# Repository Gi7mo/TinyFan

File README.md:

# Klipper TinyFan

### Navigation:
|[• Installation & Klipper](./Klipper)|[• Get a PCB](./PCB)|[• Mounts](./STL)|
|---|---|---|

|[• CAD Files](./CAD)|[• Manual](./TinyFan_Pinout.pdf)|[• Pictures](./Images)|
|---|---|---|
<br>

**ATTENTION**<br>
The LDO is flipped in the image, please don't mount it with the fin outward the pcb<br>
it must be mounted inward, so 180° flipped to shown in the image

<br>

## Notes
- Many thanks to [Rama](https://github.com/Ramalama2) who came up with the initial idea and supported me a lot.
- You can contact me via Discord "Gi7mo!#4618"
- This project does not come with any warranty, if you choose to build/use one, you are doing this at your own risk!

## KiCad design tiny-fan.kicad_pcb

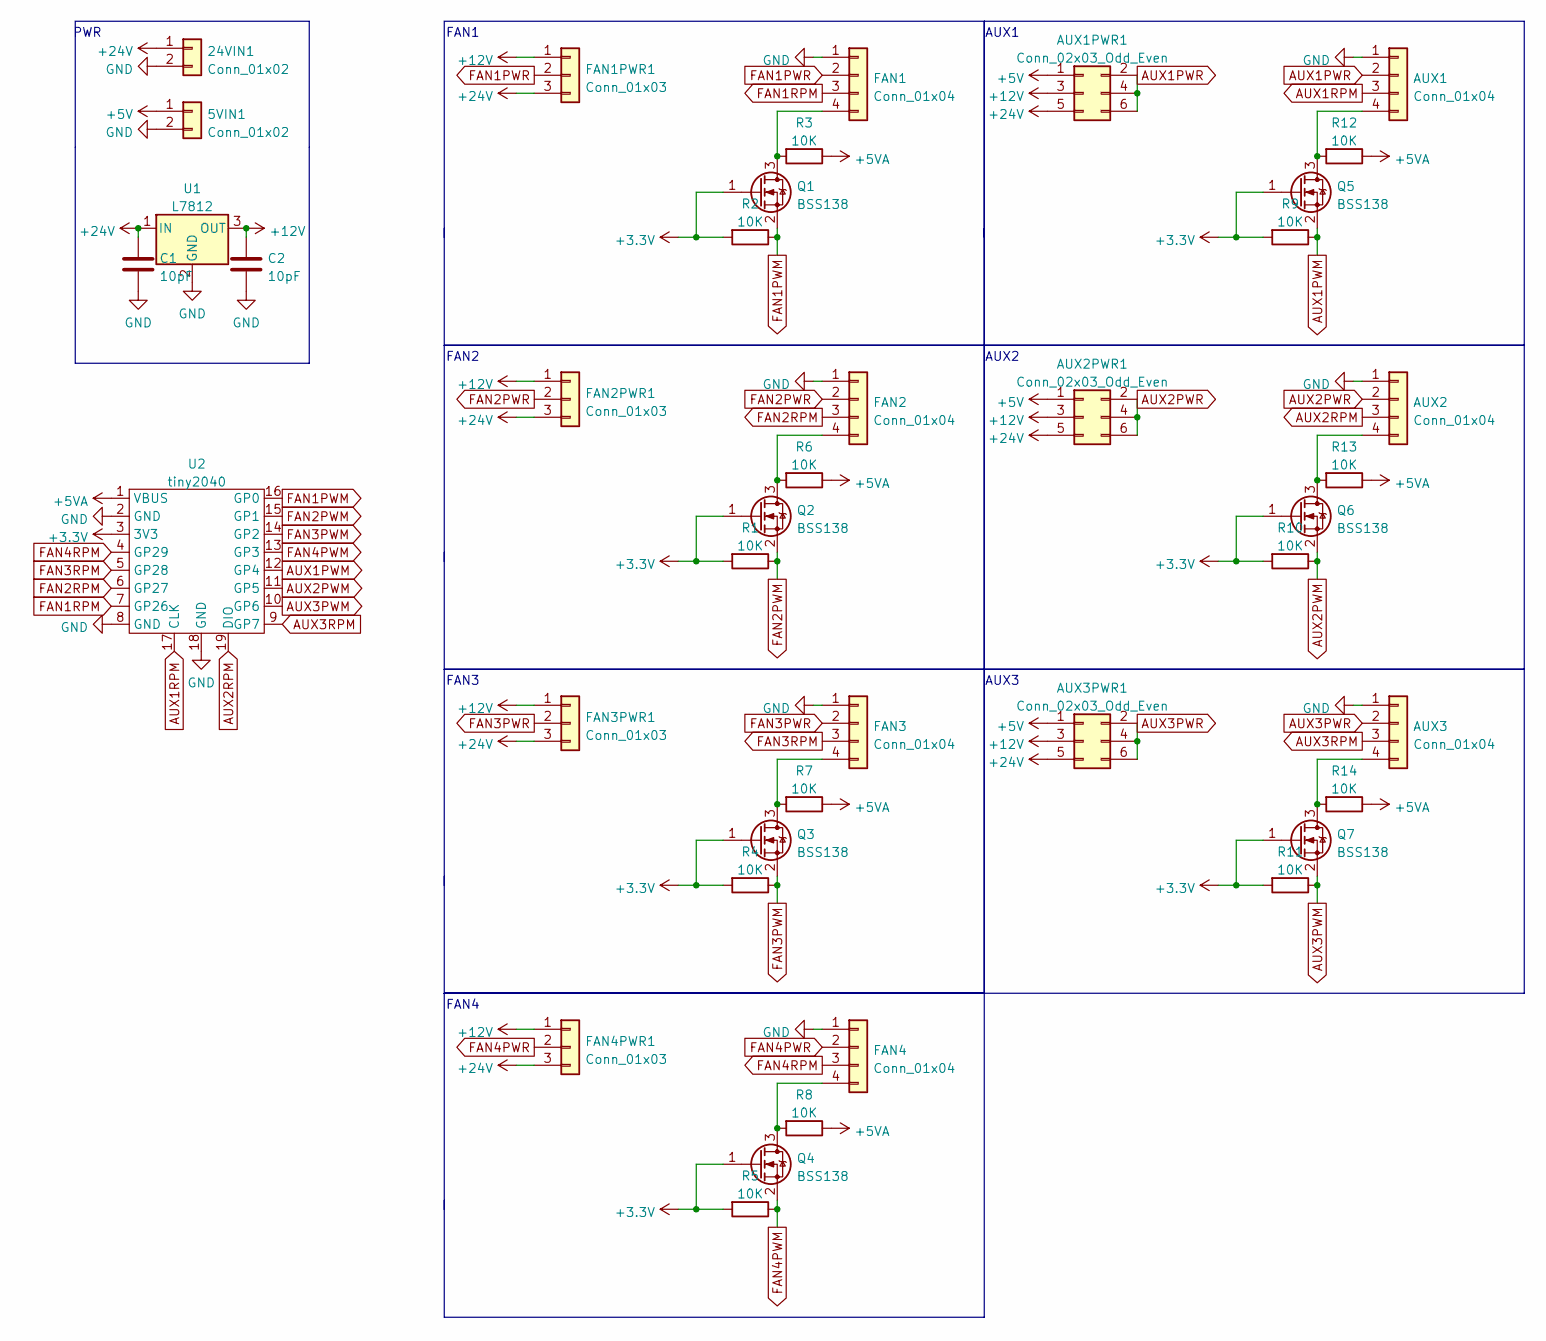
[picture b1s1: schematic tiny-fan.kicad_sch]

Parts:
5VIN1, 24VIN1: Conn_01x02; TerminalBlock_Phoenix_MKDS-1,5-2-5.08_1x02_P5.08mm_Horizont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; LCSC C475092
AUX1, AUX2, AUX3: Conn_01x04; JST_XH_B4B-XH-AM_1x04_P2.50mm_Vertical; LCSC C161871
AUX1PWR1, AUX2PWR1, AUX3PWR1: Conn_02x03_Odd_Even; PinHeader_2x03_P2.54mm_Vertical; LCSC C492420
C1, C2: 10pF; C_1206_3216Metric; LCSC C107172
FAN1, FAN2, FAN3, FAN4: Conn_01x04; FanPinHeader_1x04_P2.54mm_Vertical; LCSC C402778
FAN1PWR1, FAN2PWR1, FAN3PWR1, FAN4PWR1: Conn_01x03; PinHeader_1x03_P2.54mm_Vertical; LCSC C2937625
Q1, Q2, Q3, Q4, Q5, Q6, Q7: BSS138; SOT-23; LCSC C52895
R1, R2, R3, R4, R5, R6, R7, R8, R9, R10, R11, R12, R13, R14: 10K; R_1206_3216Metric; LCSC C144471
U1: L7812; TO-220-3; LCSC C105651
U2: tiny2040

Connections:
+3V3: Q1.1 (G), Q2.1 (G), Q3.1 (G), Q4.1 (G), Q5.1 (G), Q6.1 (G), Q7.1 (G), R1.2, R2.2, R4.2, R5.2, R9.2, R10.2, R11.2, U2.3 (3V3)
+5V: 5VIN1.1, AUX1PWR1.1, AUX2PWR1.1, AUX3PWR1.1
+5VA: R3.1, R6.1, R7.1, R8.1, R12.1, R13.1, R14.1, U2.1 (VBUS)
+12V: AUX1PWR1.3, AUX2PWR1.3, AUX3PWR1.3, C2.1, FAN1PWR1.1, FAN2PWR1.1, FAN3PWR1.1, FAN4PWR1.1, U1.3 (OUT)
+24V: 24VIN1.1, AUX1PWR1.5, AUX2PWR1.5, AUX3PWR1.5, C1.1, FAN1PWR1.3, FAN2PWR1.3, FAN3PWR1.3, FAN4PWR1.3, U1.1 (IN)
AUX1PWM: Q5.2 (S), R9.1, U2.12 (GP4)
AUX1PWR: AUX1.2, AUX1PWR1.2, AUX1PWR1.4, AUX1PWR1.6
AUX1RPM: AUX1.3, U2.17 (CLK)
AUX2PWM: Q6.2 (S), R10.1, U2.11 (GP5)
AUX2PWR: AUX2.2, AUX2PWR1.2, AUX2PWR1.4, AUX2PWR1.6
AUX2RPM: AUX2.3, U2.19 (DIO)
AUX3PWM: Q7.2 (S), R11.1, U2.10 (GP6)
AUX3PWR: AUX3.2, AUX3PWR1.2, AUX3PWR1.4, AUX3PWR1.6
AUX3RPM: AUX3.3, U2.9 (GP7)
FAN1PWM: Q1.2 (S), R2.1, U2.16 (GP0)
FAN1PWR: FAN1.2, FAN1PWR1.2
FAN1RPM: FAN1.3, U2.7 (GP26)
FAN2PWM: Q2.2 (S), R1.1, U2.15 (GP1)
FAN2PWR: FAN2.2, FAN2PWR1.2
FAN2RPM: FAN2.3, U2.6 (GP27)
FAN3PWM: Q3.2 (S), R4.1, U2.14 (GP2)
FAN3PWR: FAN3.2, FAN3PWR1.2
FAN3RPM: FAN3.3, U2.5 (GP28)
FAN4PWM: Q4.2 (S), R5.1, U2.13 (GP3)
FAN4PWR: FAN4.2, FAN4PWR1.2
FAN4RPM: FAN4.3, U2.4 (GP29)
GND: 5VIN1.2, 24VIN1.2, AUX1.1, AUX2.1, AUX3.1, C1.2, C2.2, FAN1.1, FAN2.1, FAN3.1, FAN4.1, U1.2 (GND), U2.2 (GND), U2.8 (GND), U2.18 (GND); also elsewhere on the board
unnamed: AUX1.4, Q5.3 (D), R12.2
unnamed: AUX2.4, Q6.3 (D), R13.2
unnamed: AUX3.4, Q7.3 (D), R14.2
unnamed: FAN1.4, Q1.3 (D), R3.2
unnamed: FAN2.4, Q2.3 (D), R6.2
unnamed: FAN3.4, Q3.3 (D), R7.2
unnamed: FAN4.4, Q4.3 (D), R8.2

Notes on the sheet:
AUX3
FAN1
AUX1
AUX2
FAN4
FAN3
FAN2
PWR

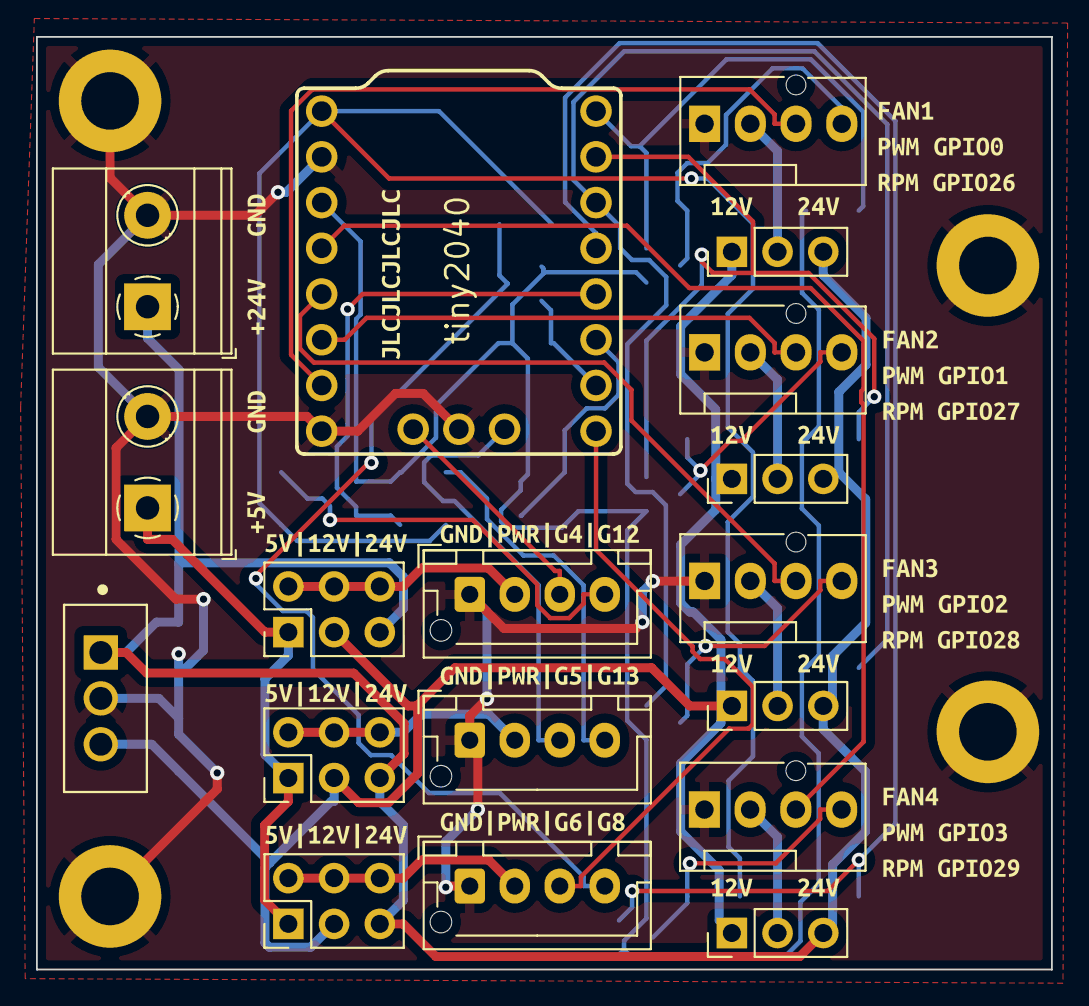
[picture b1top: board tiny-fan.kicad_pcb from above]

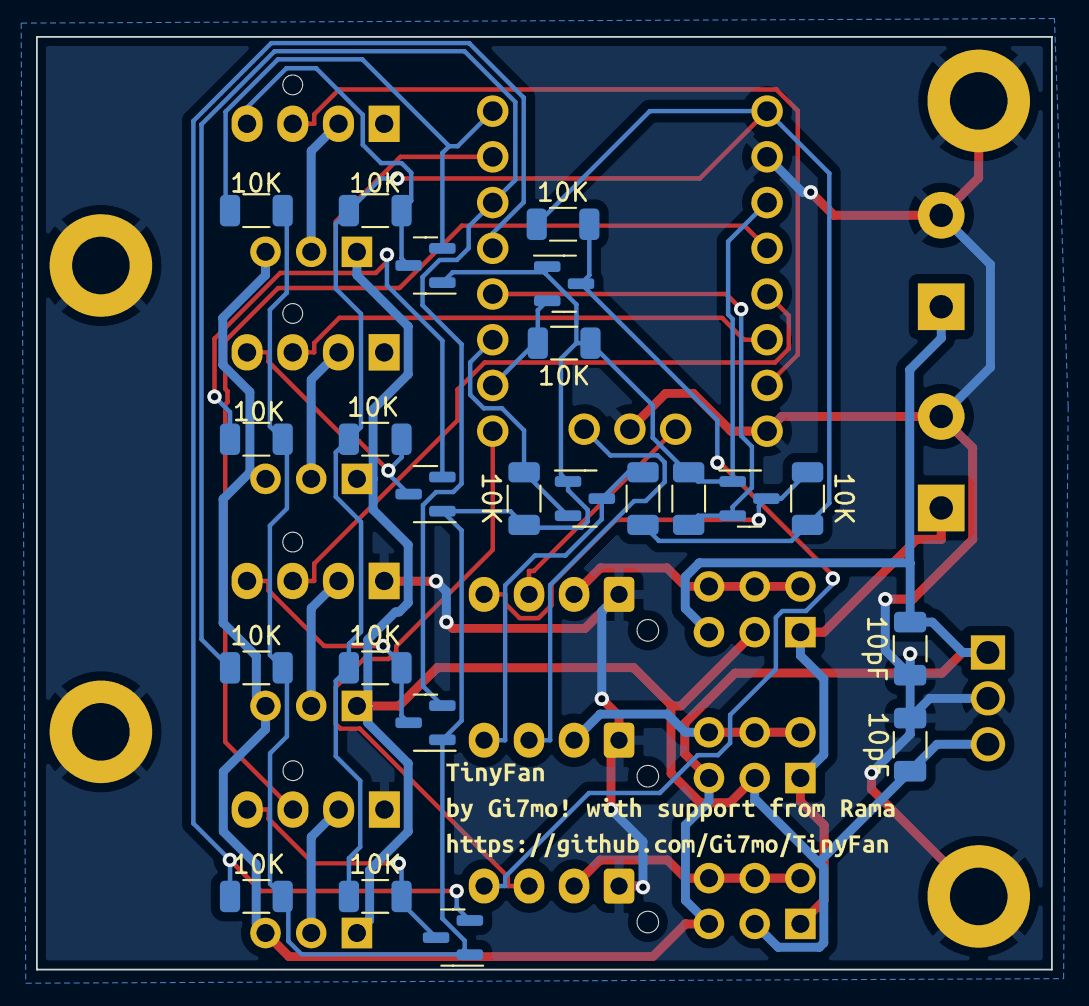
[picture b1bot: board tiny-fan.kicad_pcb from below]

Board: 2 copper layers, 56.4 x 51.8 mm, 69 parts (24 on the bottom side), 34 nets.

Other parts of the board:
REF1, REF2, REF3, REF4: MountingHole_3.2mm_M3_ISO7380_Pad
kibuzzard-62F4A92A: G***; kibuzzard-62F4A92A
kibuzzard-62F4AAD2: G***; kibuzzard-62F4AAD2
kibuzzard-62F4E43D: G***; kibuzzard-62F4E43D
kibuzzard-62F4E44F: G***; kibuzzard-62F4E44F
kibuzzard-62F4E423: G***; kibuzzard-62F4E423
kibuzzard-62F42A54: G***; kibuzzard-62F42A54
kibuzzard-62F42B83: G***; kibuzzard-62F42B83
kibuzzard-62F42B98: G***; kibuzzard-62F42B98
kibuzzard-62F42BB7: G***; kibuzzard-62F42BB7
kibuzzard-62F425A2: G***; kibuzzard-62F425A2
kibuzzard-62F425B31: G***; kibuzzard-62F425B3
kibuzzard-62F425BF: G***; kibuzzard-62F425BF
kibuzzard-62F4287A, kibuzzard-62F4287AA, kibuzzard-62F4287AB, kibuzzard-62F4287AC: G***; kibuzzard-62F4287A
kibuzzard-62F42591: G***; kibuzzard-62F42591
kibuzzard-62F42661, kibuzzard-62F426612, kibuzzard-62F426613: G***; kibuzzard-62F42661
kibuzzard-62F42888, kibuzzard-62F428881, kibuzzard-62F428884, kibuzzard-62F4288845: G***; kibuzzard-62F42888

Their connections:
GND: REF1.1, REF2.1, REF3.1, REF4.1; also elsewhere on the board

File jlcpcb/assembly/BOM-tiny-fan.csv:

Comment,Designator,Footprint,LCSC
10pF,"C1,C2",C_1206_3216Metric,C107172
10K,"R1,R10,R11,R12,R13,R14,R2,R3,R4,R5,R6,R7,R8,R9",R_1206_3216Metric,C144471
BSS138,"Q1,Q2,Q3,Q4,Q5,Q6,Q7",SOT-23,C52895
tiny2040,U2,tiny2040,
Conn_01x02,5VIN1,"TerminalBlock_Phoenix_MKDS-1,5-2-5.08_1x02_P5.08mm_Horizontal",
Conn_01x04,FAN4,FanPinHeader_1x04_P2.54mm_Vertical,
Conn_01x04,FAN3,FanPinHeader_1x04_P2.54mm_Vertical,
Conn_01x04,FAN2,FanPinHeader_1x04_P2.54mm_Vertical,
Conn_01x04,FAN1,FanPinHeader_1x04_P2.54mm_Vertical,
Conn_01x03,FAN4PWR1,PinHeader_1x03_P2.54mm_Vertical,
Conn_01x03,FAN3PWR1,PinHeader_1x03_P2.54mm_Vertical,
Conn_01x03,FAN2PWR1,PinHeader_1x03_P2.54mm_Vertical,
L7812,U1,TO-220-3,
Conn_01x02,24VIN1,"TerminalBlock_Phoenix_MKDS-1,5-2-5.08_1x02_P5.08mm_Horizontal",
Conn_02x03_Odd_Even,AUX3PWR1,PinHeader_2x03_P2.54mm_Vertical,
Conn_02x03_Odd_Even,AUX2PWR1,PinHeader_2x03_P2.54mm_Vertical,
Conn_02x03_Odd_Even,AUX1PWR1,PinHeader_2x03_P2.54mm_Vertical,
Conn_01x04,AUX3,JST_XH_B4B-XH-AM_1x04_P2.50mm_Vertical,
Conn_01x04,AUX2,JST_XH_B4B-XH-AM_1x04_P2.50mm_Vertical,
Conn_01x04,AUX1,JST_XH_B4B-XH-AM_1x04_P2.50mm_Vertical,
Conn_01x03,FAN1PWR1,PinHeader_1x03_P2.54mm_Vertical,

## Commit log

2022-08-13 initial
2022-09-01 version 2
2022-09-11 cleanup repo and add useable readme
2022-09-12 Fix: typo in README.md
2022-09-12 fix cad
2022-09-15 Part 1 of 2 from Rama with Love :-)
    Mounts etc
2022-09-18 Part 2 of 2 from Rama with Love :-)
    Extrusion Mounts were updated, they are now 1mm thicker, because the screw scraped the extrusion before.
2022-09-18 Update LICENSE
2022-09-19 Small Fixes Everywhere
    - Updated images for Consistency
    - Updated Cad Files
    - Updated Example Config
    - Fixes here and there, blahblah :-)
2022-09-19 Config Example Fix
2022-09-19 Fixes Fixes
    Just some Image updates
2022-09-25 remove thermistor option
